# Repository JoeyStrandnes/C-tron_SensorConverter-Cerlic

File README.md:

# C-tron_SensorConverter-Cerlic

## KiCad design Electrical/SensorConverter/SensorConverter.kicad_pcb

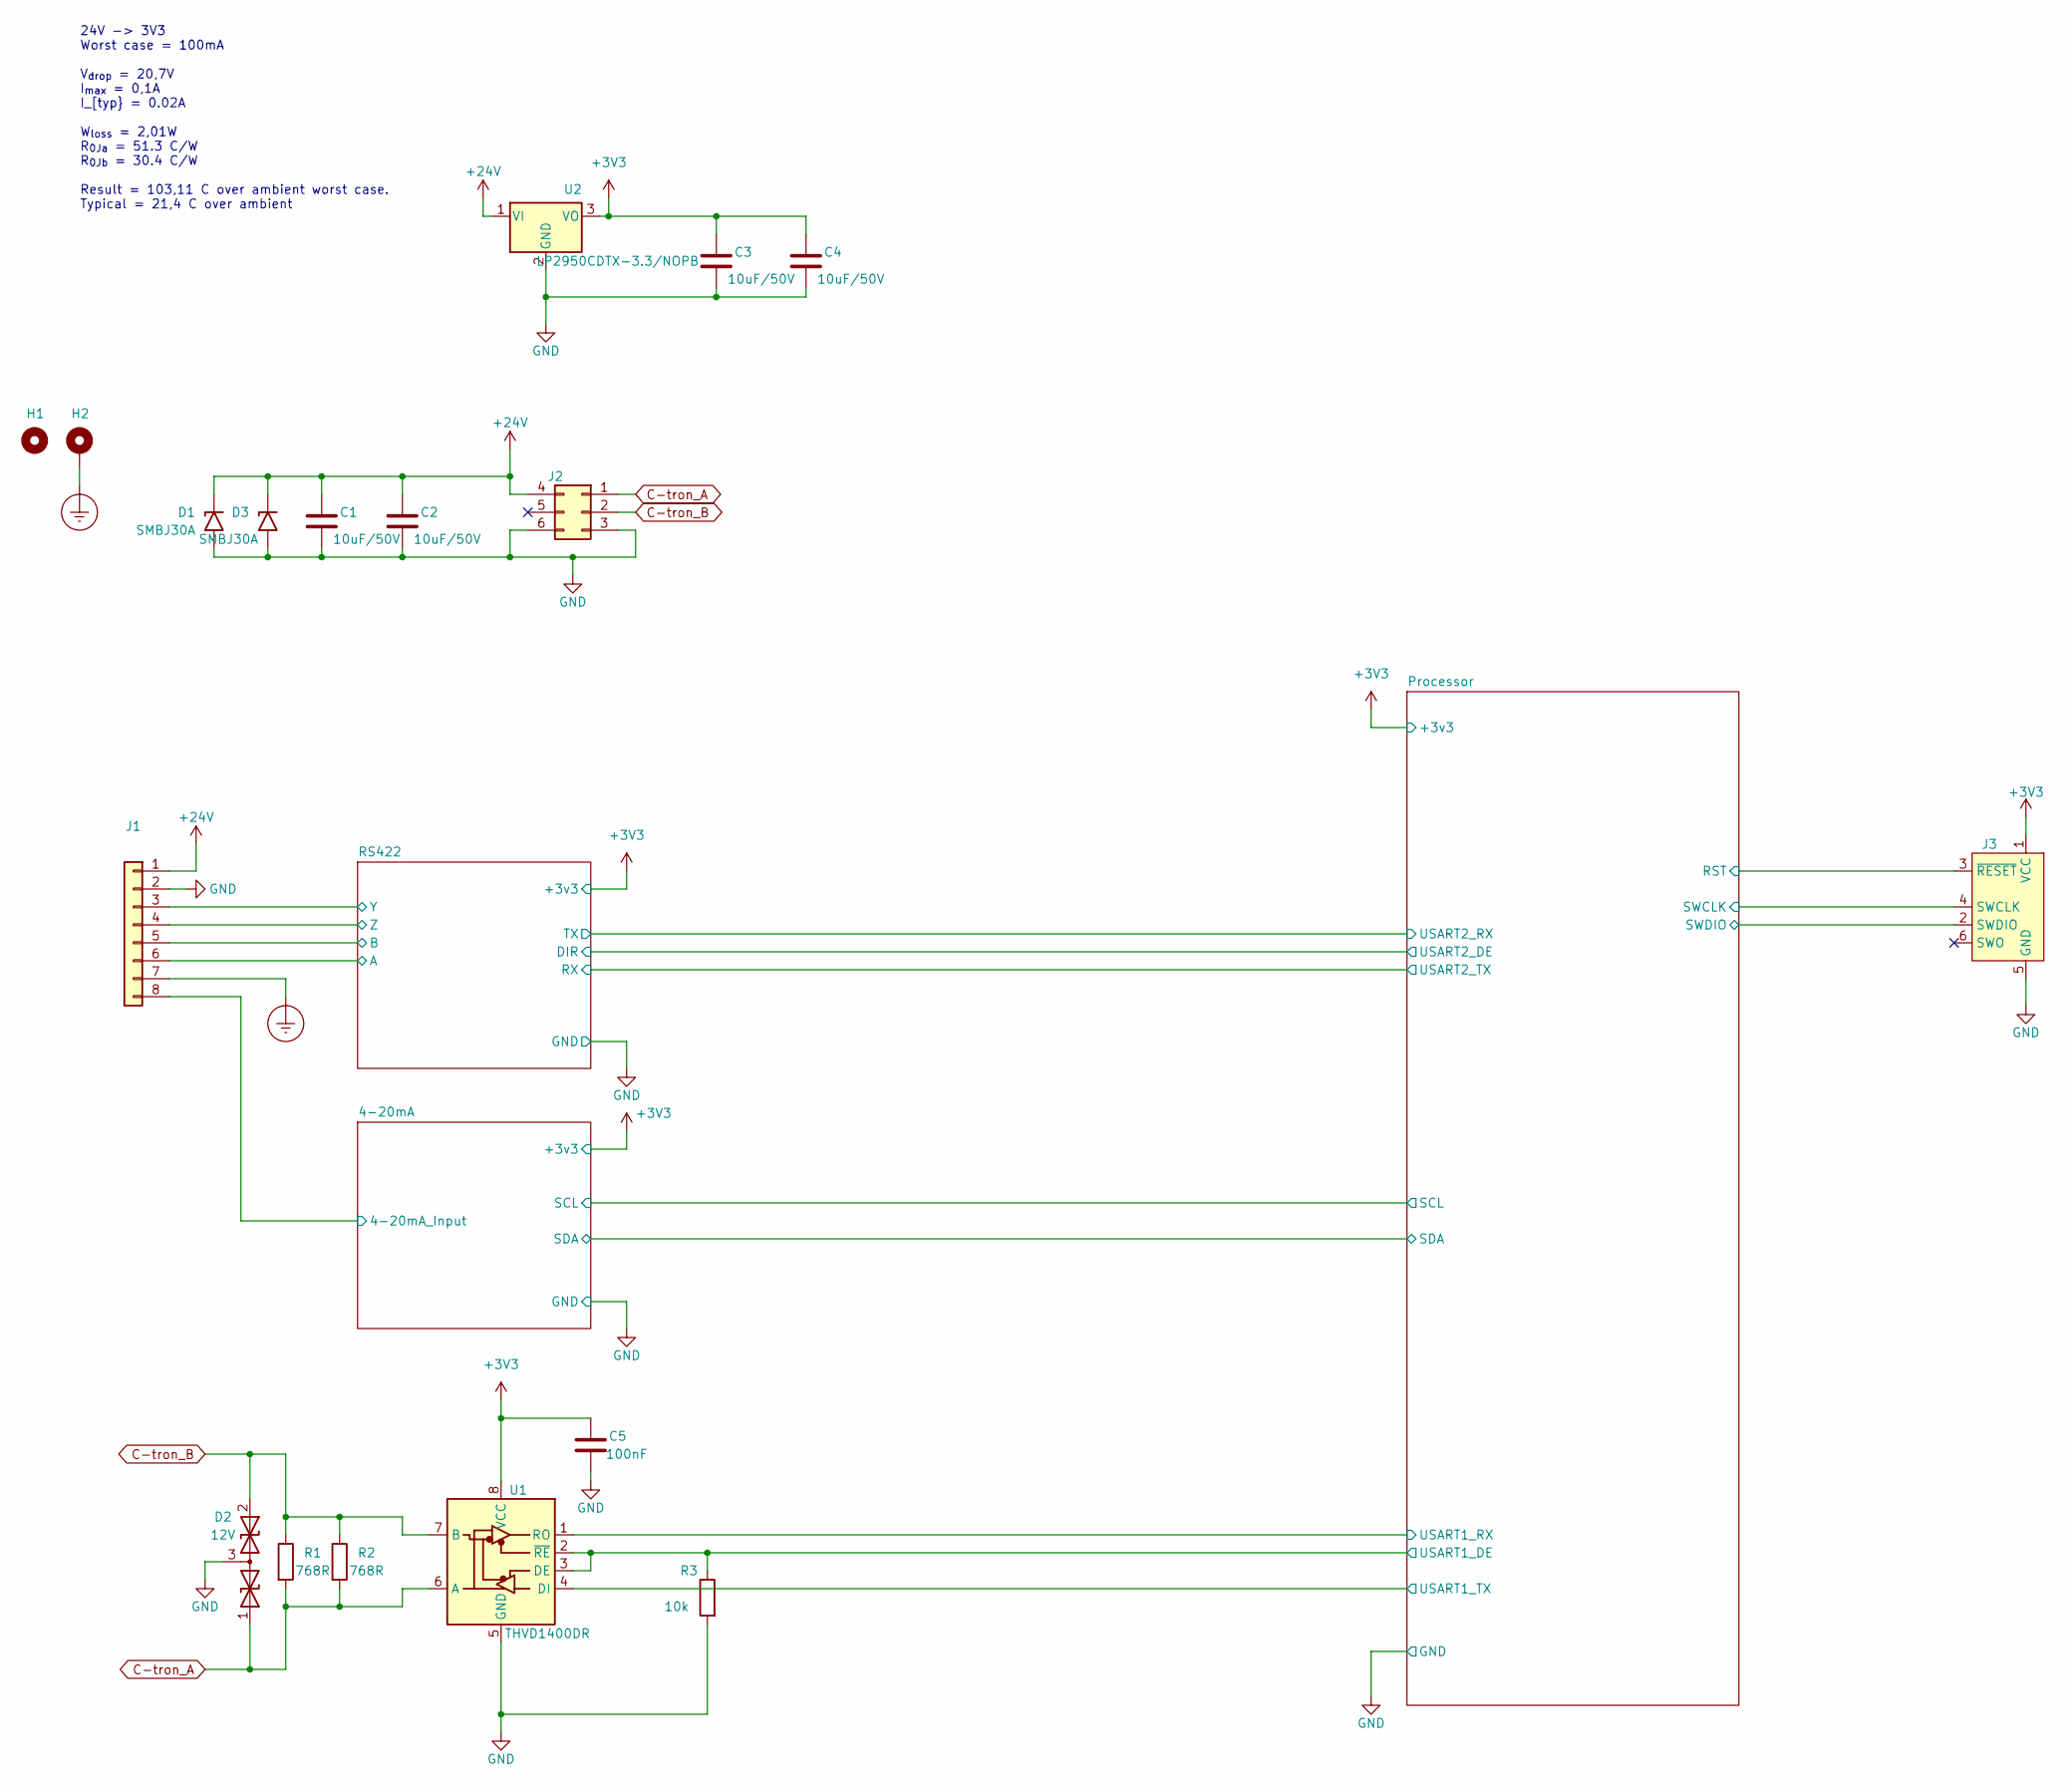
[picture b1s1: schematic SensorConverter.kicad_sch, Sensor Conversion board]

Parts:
C1, C2, C3, C4: 10uF/50V; C_1206_3216Metric
C5: 100nF; C_0402_1005Metric; Voltage 25V
D1, D3: SMBJ30A; D_SMB
D2: 12V; SOT-323_SC-70; MPN DF3D18FU,LF
H1: MountingHole; MountingHole_3.2mm_M3
H2: MountingHole_Pad; MountingHole_3.2mm_M3_DIN965_Pad
J1: 1990067
J2: 0430450600
J3: Conn_ARM_SWD_TagConnect_TC2030-NL; Tag-Connect_TC2030-IDC-NL_2x03_P1.27mm_Vertical
R1, R2: 768R; R_0603_1608Metric
R3: 10k; R_0402_1005Metric
U1: THVD1400DR; SOIC-8_3.9x4.9mm_P1.27mm
U2: LP2950CDTX-3.3/NOPB; TO-252-2

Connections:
+3V3: C3.2, C4.2, C5.2, J3.1 (VCC), U1.8 (VCC), U2.3 (VO); also elsewhere on the board
+24V: C1.2, C2.2, D1.1 (A1), D3.1 (A1), J1.1, J2.4, U2.1 (VI)
/4-20mA/4-20mA_Input: J1.8; also elsewhere on the board
/Processor/RST: J3.3 (~RESET); also elsewhere on the board
/Processor/SWCLK: J3.4 (SWCLK); also elsewhere on the board
/Processor/SWDIO: J3.2 (SWDIO); also elsewhere on the board
/Processor/USART1_DE: R3.1, U1.2 (~RE), U1.3 (DE); also elsewhere on the board
/Processor/USART1_RX: U1.1 (RO); also elsewhere on the board
/Processor/USART1_TX: U1.4 (DI); also elsewhere on the board
/RS422/A: J1.6; also elsewhere on the board
/RS422/B: J1.5; also elsewhere on the board
/RS422/Y: J1.3; also elsewhere on the board
/RS422/Z: J1.4; also elsewhere on the board
C-tron_A: D2.1 (A1), J2.1, R1.2, R2.2, U1.6 (A)
C-tron_B: D2.2 (A2), J2.2, R1.1, R2.1, U1.7 (B)
Earth_Protective: H2.1, J1.7
GND: C1.1, C2.1, C3.1, C4.1, C5.1, D1.2 (A2), D2.3 (common), D3.2 (A2), J1.2, J2.3, J2.6, J3.5 (GND), R3.2, U1.5 (GND), U2.2 (GND); also elsewhere on the board

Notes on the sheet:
24V -> 3V3 Worst case = 100mA V_{drop} = 20,7V I_{max} = 0,1A I_[typ} = 0.02A W_{loss} = 2,01W R_{0Ja} = 51.3 C/W R_{0Jb} = 30.4 C/W Result = 103,11 C over ambient worst case. Typical = 21,4 C over ambient

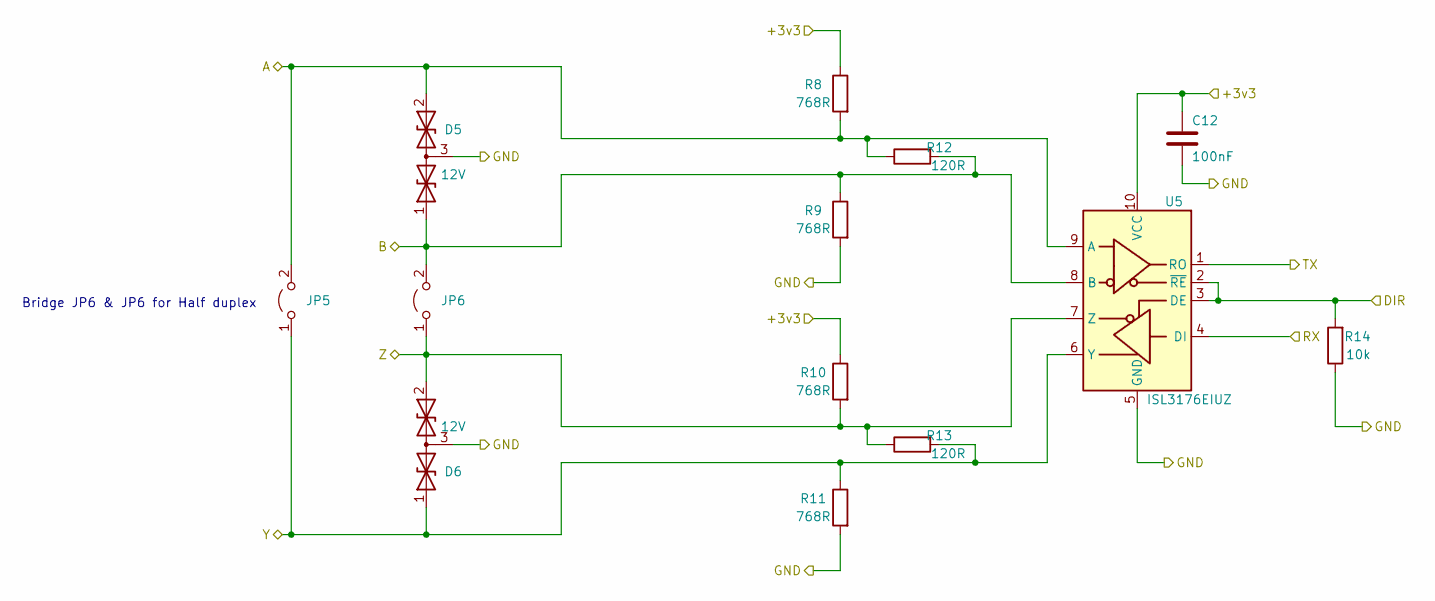
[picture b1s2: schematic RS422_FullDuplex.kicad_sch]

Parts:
C12: 100nF; C_0402_1005Metric; Voltage 50V
D5, D6: 12V; SOT-323_SC-70; MPN DF3D18FU,LF
JP5, JP6: Jumper_2_Open; SolderJumper-2_P1.3mm_Open_RoundedPad1.0x1.5mm
R8, R9, R10, R11: 768R; R_0603_1608Metric
R12, R13: 120R; R_0603_1608Metric
R14: 10k; R_0402_1005Metric
U5: ISL3176EIUZ; TSSOP-10_3x3mm_P0.5mm

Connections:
+3V3: C12.1, R8.1, R10.1, U5.10 (VCC); also elsewhere on the board
/Processor/USART2_DE: R14.2, U5.2 (~RE), U5.3 (DE); also elsewhere on the board
/Processor/USART2_RX: U5.1 (RO); also elsewhere on the board
/Processor/USART2_TX: U5.4 (DI); also elsewhere on the board
/RS422/A: D5.2 (A2), JP5.2 (B), R8.2, R12.1, U5.9 (A); also elsewhere on the board
/RS422/B: D5.1 (A1), JP6.2 (B), R9.1, R12.2, U5.8 (B); also elsewhere on the board
/RS422/Y: D6.1 (A1), JP5.1 (A), R11.1, R13.2, U5.6 (Y); also elsewhere on the board
/RS422/Z: D6.2 (A2), JP6.1 (A), R10.2, R13.1, U5.7 (Z); also elsewhere on the board
GND: C12.2, D5.3 (common), D6.3 (common), R9.2, R11.2, R14.1, U5.5 (GND); also elsewhere on the board

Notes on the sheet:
Bridge JP6 & JP6 for Half duplex

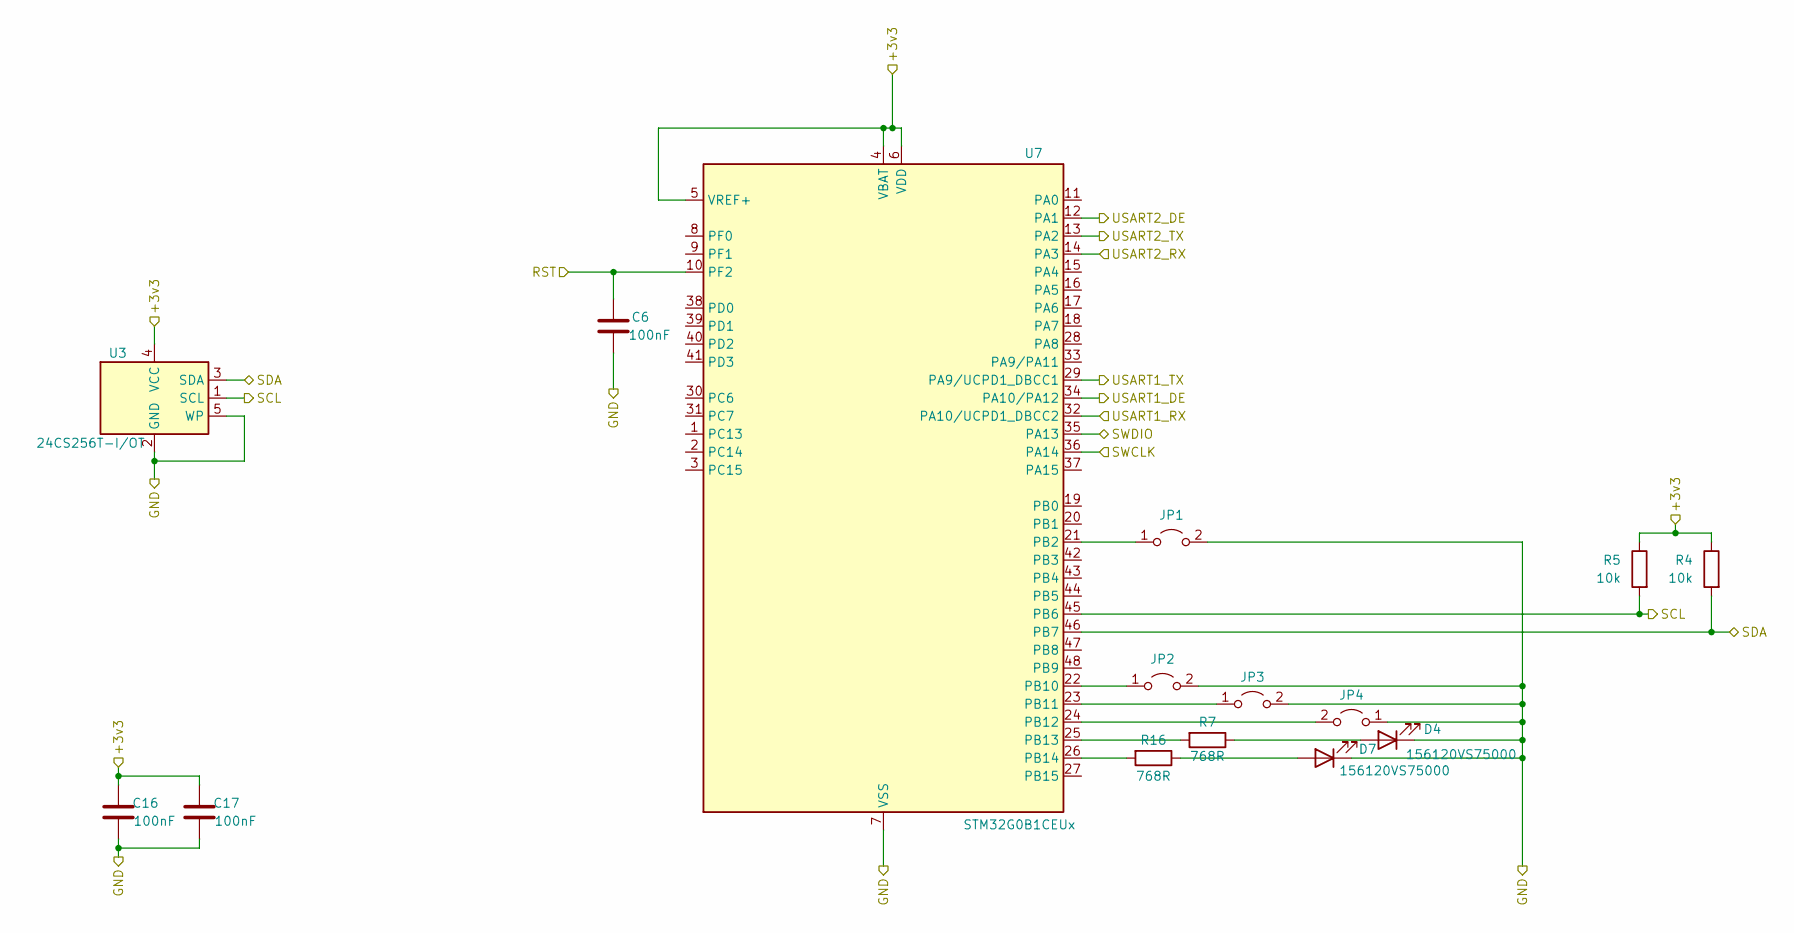
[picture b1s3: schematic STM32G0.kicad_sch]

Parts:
C6, C16, C17: 100nF; C_0402_1005Metric; Voltage 25V
D4, D7: 156120VS75000; WL-SMRW
JP1, JP2, JP3, JP4: Jumper_2_Open; SolderJumper-2_P1.3mm_Open_RoundedPad1.0x1.5mm
R4, R5: 10k; R_0402_1005Metric
R7, R16: 768R; R_0603_1608Metric
U3: 24CS256T-I/OT; SOT-23-5
U7: STM32G0B1CEUx; QFN-48-1EP_7x7mm_P0.5mm_EP5.6x5.6mm

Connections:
+3V3: C16.2, C17.2, R4.1, R5.1, U3.4 (VCC), U7.4 (VBAT), U7.5 (VREF+), U7.6 (VDD); also elsewhere on the board
/4-20mA/SCL: R5.2, U3.1 (SCL), U7.45 (PB6); also elsewhere on the board
/4-20mA/SDA: R4.2, U3.3 (SDA), U7.46 (PB7); also elsewhere on the board
/Processor/RST: C6.2, U7.10 (PF2); also elsewhere on the board
/Processor/SWCLK: U7.36 (PA14); also elsewhere on the board
/Processor/SWDIO: U7.35 (PA13); also elsewhere on the board
/Processor/USART1_DE: U7.34 (PA10/PA12); also elsewhere on the board
/Processor/USART1_RX: U7.32 (PA10/UCPD1_DBCC2); also elsewhere on the board
/Processor/USART1_TX: U7.29 (PA9/UCPD1_DBCC1); also elsewhere on the board
/Processor/USART2_DE: U7.12 (PA1); also elsewhere on the board
/Processor/USART2_RX: U7.14 (PA3); also elsewhere on the board
/Processor/USART2_TX: U7.13 (PA2); also elsewhere on the board
GND: C6.1, C16.1, C17.1, D4.1 (K), D7.1 (K), JP1.2 (B), JP2.2 (B), JP3.2 (B), JP4.1 (A), U3.2 (GND), U3.5 (WP), U7.7 (VSS), U7.49 (VSS); also elsewhere on the board
unnamed: D4.2 (A), R7.1
unnamed: D7.2 (A), R16.1
unnamed: JP1.1 (A), U7.21 (PB2)
unnamed: JP2.1 (A), U7.22 (PB10)
unnamed: JP3.1 (A), U7.23 (PB11)
unnamed: JP4.2 (B), U7.24 (PB12)
unnamed: R7.2, U7.25 (PB13)
unnamed: R16.2, U7.26 (PB14)

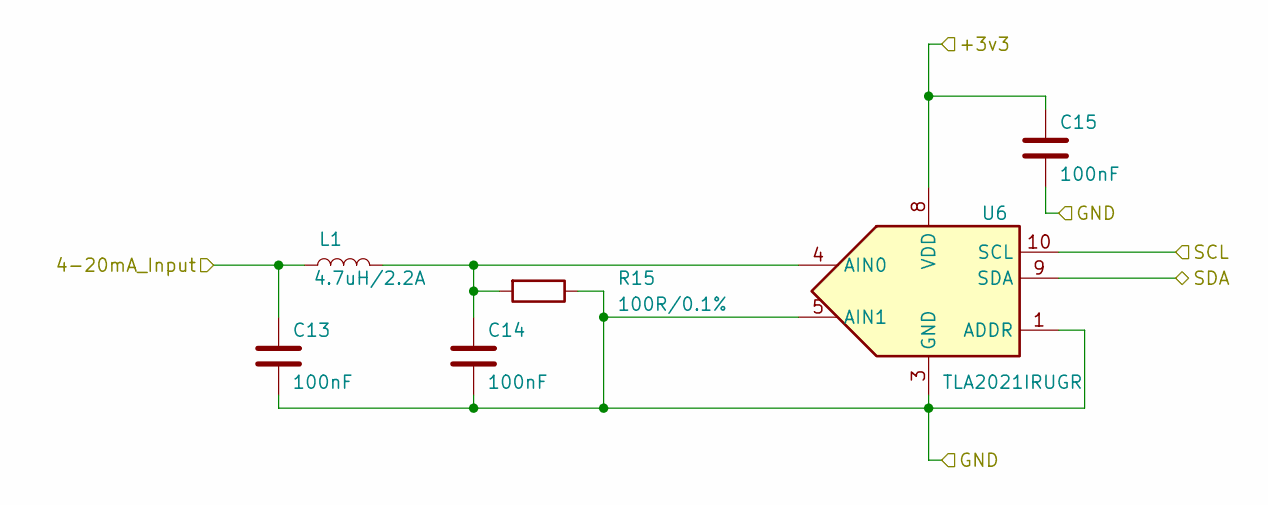
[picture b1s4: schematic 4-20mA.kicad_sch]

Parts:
C13, C14, C15: 100nF; C_0402_1005Metric; Voltage 50V
L1: 4.7uH/2.2A; L_1210_3225Metric; MPN SRP3212-4R7M
R15: 100R/0.1%; R_0603_1608Metric
U6: TLA2021IRUGR; Texas_R-PUQFN-N10

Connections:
+3V3: C15.1, U6.8 (VDD); also elsewhere on the board
/4-20mA/4-20mA_Input: C13.1, L1.1; also elsewhere on the board
/4-20mA/SCL: U6.10 (SCL); also elsewhere on the board
/4-20mA/SDA: U6.9 (SDA); also elsewhere on the board
GND: C13.2, C14.2, C15.2, R15.1, U6.1 (ADDR), U6.3 (GND), U6.5 (AIN1); also elsewhere on the board
unnamed: C14.1, L1.2, R15.2, U6.4 (AIN0)

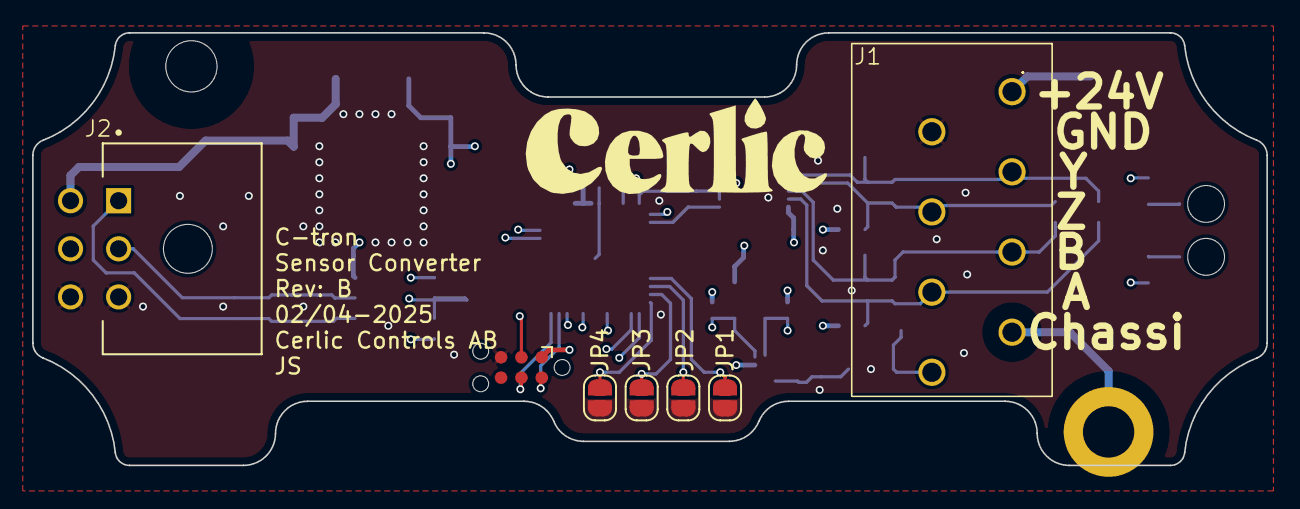
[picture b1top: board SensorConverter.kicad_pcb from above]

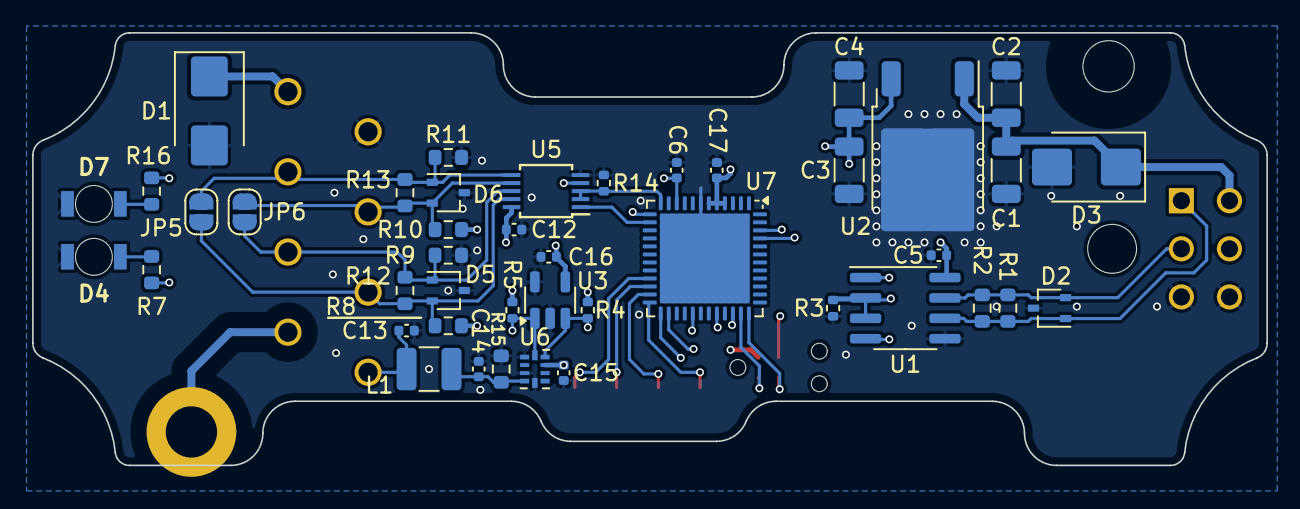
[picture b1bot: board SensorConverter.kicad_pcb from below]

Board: 4 copper layers, 77.0 x 27.0 mm, 52 parts (43 on the bottom side), 31 nets.

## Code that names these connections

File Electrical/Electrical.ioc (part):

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Mcu.Name=STM32G0B1C(B-C-E)Ux
Mcu.Package=UFQFPN48
Mcu.UserName=STM32G0B1CEUx
PA1.Mode=Hardware Flow Control (RS485)
PA1.Signal=USART2_DE
PA10.Mode=Asynchronous
PA10.Signal=USART1_RX
PA11\ [PA9].Mode=Device
PA11\ [PA9].Signal=USB_DM
PA12\ [PA10].Mode=Device
PA12\ [PA10].Signal=USB_DP
PA13.Mode=Serial_Wire
PA13.Signal=SYS_SWDIO
PA14-BOOT0.Mode=Serial_Wire
PA14-BOOT0.Signal=SYS_SWCLK
PA2.Mode=Asynchronous
PA2.Signal=USART2_TX
PA3.Mode=Asynchronous
PA3.Signal=USART2_RX
PA9.Mode=Asynchronous
PA9.Signal=USART1_TX
PB10.GPIOParameters=GPIO_PuPd,GPIO_Label
PB10.GPIO_Label=JP2
PB10.GPIO_PuPd=GPIO_PULLUP
PB10.Signal=GPIO_Input
PB11.GPIOParameters=GPIO_PuPd,GPIO_Label
PB11.GPIO_Label=JP3
PB11.GPIO_PuPd=GPIO_PULLUP
PB11.Signal=GPIO_Input
PB12.GPIOParameters=GPIO_PuPd,GPIO_Label
PB12.GPIO_Label=JP4
PB12.GPIO_PuPd=GPIO_PULLUP
PB12.Signal=GPIO_Input
PB13.Signal=GPIO_Output
PB14.GPIOParameters=GPIO_Label
PB14.GPIO_Label=LED_2
PB14.Signal=GPIO_Output
PB2.Signal=GPIO_Input
PB3.Mode=Hardware Flow Control (RS485)
PB3.Signal=USART1_DE
PB6.Mode=I2C
PB6.Signal=I2C1_SCL
PB7.Mode=I2C
PB7.Signal=I2C1_SDA
RCC.HSE_VALUE=8000000
RCC.SYSCLKFreq_VALUE=64000000
RCC.SYSCLKSource=RCC_SYSCLKSOURCE_PLLCLK
board=custom

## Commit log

2025-03-11 Project init
2025-03-11 Updated gitignore
2025-03-11 More initial setup
2025-03-11 Added DMA to the UART channels
2025-03-11 Minor configuration
2025-03-11 Setting up the master & slave registers
2025-03-12 Very basic Modbus stack working
2025-03-12 More work on communication
2025-03-12 Working IT driven COM. DMA not so much
2025-03-12 Added more ModBus functions
2025-03-12 Proof of concept working
2025-03-17 Revamping the ModBus system
2025-03-17 More work on Modbus Stack
2025-03-17 Working ModBus bridge implementation
2025-03-17 Minor changes to ModBus structure
2025-03-18 Removed UART DMA
2025-03-18 Start transmitting after a set period
2025-03-18 C-tron communication not really working
2025-03-18 Fixed formatting bug
2025-03-18 Updated register map for more paramters
2025-03-18 More testing
2025-03-18 Adjusted data mapping
2025-03-18 Working on the NVM system
2025-03-18 General work to the NVM and Modbus stack
2025-03-18 More work to writing to NVM
2025-03-19 Reworking UART implementation
2025-03-19 Lots of UART testing
2025-03-24 Working SW USART IDLE
2025-03-24 Fixed DIR bug
2025-03-24 Removed old code
2025-03-24 Still some issues with NVM
2025-03-24 Cleaned up the code
2025-03-24 Implemented a scalable approach for regs
2025-03-24 Working on FLX implementation
2025-03-25 Added FLX docs
2025-03-25 Fixed UART deadlock bug
2025-03-25 Added factory reset command
2025-03-25 All basic custom ModBus functions work
2025-03-25 Issues with I2C not sending data....
2025-03-25 Working on LFX flow calculations
2025-03-25 Working on a dynamic sensor system
2025-04-01 Working on the FLX calibration
2025-04-01 More FLX work
2025-04-02 Fixed register size and cleaned code
2025-04-02 Parshall flume working
    Needs more testing!
2025-04-02 Changing processor to STM32G0
    This is mostly because of memory constraints and that the F103 is having a lot of issue.
2025-04-02 Finalized PCB RevB
2025-04-03 Fixed minor changes in PCB
2025-04-03 Initialized register mapping I/O data to zero
2025-04-03 More dynamic tag erase
2025-04-04 Simplified the USART IRQ
2025-04-04 Clear UART flags when an error occors
2025-04-04 Slight code cleanup
2025-04-04 Removed I2C drivers since it is not working...
2025-04-04 Working NVM settings in internal flash
2025-04-04 Removed startup delay
2025-04-07 Working on zero/offset calibration
2025-04-07 Basic offset calibration
2025-04-07 Fixed calculation error
2025-04-07 Sensor input/raw data is now a pointer
2025-04-07 Write correct ModBus address to NVM
2025-04-07 Removed unused code
2025-04-07 Fixed incorrect formatting of TAG
2025-04-07 Fixed bug typecasting floats to ints
2025-04-14 WIP porting to new processor
2025-04-23 Working on porting code to new processor
2025-04-24 Reworking the UART
2025-04-24 Implementing CMC
2025-04-24 Somewhat working CMC implementation
2025-05-05 CMC working, not complete!
2025-05-05 CMC FC04 fully implemented
2025-05-05 Reverting back to ghetto RxToIDLE
2025-05-05 Testing ghetto uart
2025-05-05 WIP RTO configuration
2025-05-05 USART RTO working but not nice
2025-05-05 Testing
2025-05-06 Reverting back to the home made IDLE detection
2025-05-06 Minor changes to packet size
2025-05-06 Prevent calling the transmit routine unnecessarily
2025-05-06 Sending correct number of bytes
2025-05-06 Removed DMA for USART1
